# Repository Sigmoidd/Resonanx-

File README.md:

# Resonanx

**Resonanx** is the Cloudflare-ready build of the Resonance family music room for **Exodia Stage Hand**.

It is a performance-first, family-first app for music connection:

- family join-in rooms by code
- live player glow / target chord / session pulse
- gentle family reactions that feed into the sensory experience
- favorite performance saves
- solo, local duo, remote lead, remote player, and family join-in modes
- optional thermal band BLE support

## What changed in this patch

The previous family room prototype could fall back to local/shared storage. This patch adds a real Cloudflare relay path:

```txt
/api/room/:roomCode/presence
/api/room/:roomCode/live
/api/room/:roomCode/chord
/api/room/:roomCode/reaction
```

The Worker uses a Durable Object per room code. Family feedback is no longer just text:

- ✦ Spark creates a bloom pulse and soft chime.
- 👏 Applause creates a stronger bloom/audio/haptic/thermal pulse.
- ❤️ Love creates a warm halo, softer harmonic chime, haptic pattern, and optional thermal success pulse.

The language stays compassionate: family, player, performance, session, room, join-in. No medicalized family UI.

## Local dev

```bash
npm install
npm run dev
```

Local dev uses the app normally. If the `/api/room` relay is unavailable, room state falls back to local prototype storage so the UI can still be tested.

## Cloudflare deploy

```bash
npm install
npm run build
npx wrangler login
npx wrangler deploy
```

This deploys one Cloudflare Worker that serves both:

1. the React/Vite static app from `dist/`
2. the Durable Object family relay under `/api/room/...`

## Repo structure

```txt
src/App.jsx          Main Resonance / Resonanx app
src/main.jsx         Vite React entrypoint
worker/index.js      Cloudflare Worker + Durable Object relay
wrangler.toml        Cloudflare Worker config
docs/cloudflare.md   Deployment notes
```

## Cloudflare binding

`wrangler.toml` defines:

```toml
[[durable_objects.bindings]]
name = "RESONANCE_ROOMS"
class_name = "ResonanceRoom"
```

Each room code maps to its own Durable Object instance.

## GitHub quick start

```bash
git init
git add .
git commit -m "Launch Resonanx family relay build"
git branch -M main
git remote add origin https://github.com/Sigmoidd/resonanx.git
git push -u origin main
```

If the GitHub repo does not exist yet, create `Sigmoidd/resonanx` first, then run the push commands.

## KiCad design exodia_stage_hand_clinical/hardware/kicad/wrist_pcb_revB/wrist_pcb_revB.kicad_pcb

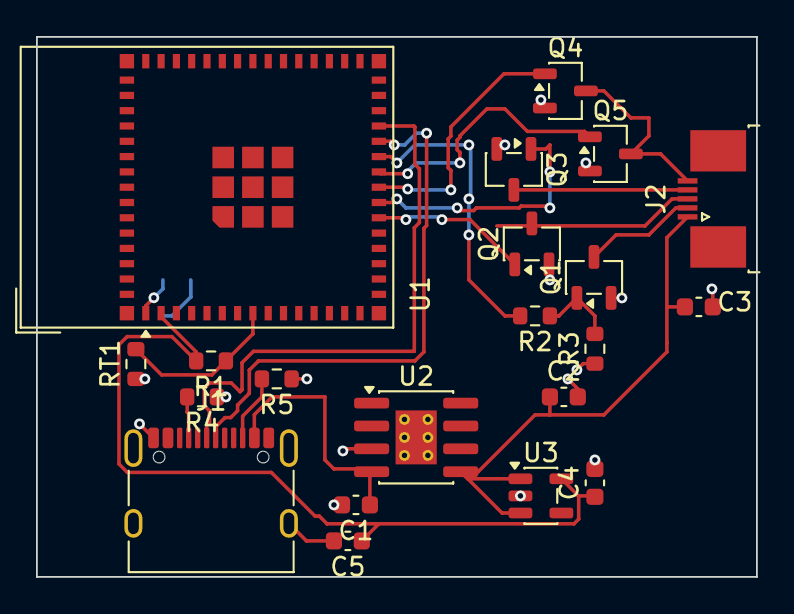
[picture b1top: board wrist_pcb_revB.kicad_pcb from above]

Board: 2 copper layers, 40.0 x 30.0 mm, 22 parts (1 on the bottom side), 19 nets.

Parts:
C1, C2, C5: 10uF; C_0603_1608Metric
C3, C4: 1uF; C_0603_1608Metric
C6: 0.1uF; C_0603_1608Metric
J1: USBC_16PIN; USB_C_Receptacle_XKB_U262-16XN-4BVC11
J2: ZIF_5PIN; TE_0-1734839-5_1x05-1MP_P0.5mm_Horizontal
Q1: AO3400A; SOT-23-3
Q2, Q3, Q4, Q5: 2N7002; SOT-23-3
R1: 10K; R_0603_1608Metric
R2: 100; R_0603_1608Metric
R3: 100K; R_0603_1608Metric
R4, R5: 5.1K; R_0603_1608Metric
RT1: NTC; R_0603_1608Metric
U1: ESP32S3_MODULE; ESP32-S2-MINI-1
U2: TP4056_IC; SOIC-8-1EP_3.9x4.9mm_P1.27mm_EP2.29x3mm_ThermalVias
U3: AP2112K; SOT-23-5

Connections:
/3V3: C4.1, C5.1, C6.1, R1.2, U1.2 (3V3), U3.5 (VOUT)
/ADC_NTC: R1.1, RT1.2, U1.8 (ADC_NTC)
/BAT+: C2.1, C3.1, J2.1 (V+), U2.5 (BAT+), U3.1 (VIN), U3.3 (EN)
/GATE_HEAT: Q1.1 (G), R2.1, R3.2
/GND: C1.2, C2.2, C3.2, C4.2, C5.2, C6.2, J1.A1 (GND), J1.A12 (GND), J1.B1 (GND), J1.B12 (GND), J1.SH (SHIELD), Q1.2 (S), Q2.2 (S), Q3.2 (S), Q4.2 (S), Q5.2 (S), R3.1, R4.1, R5.1, RT1.1, U1.1 (GND), U2.3 (BAT-), U3.2 (GND)
/NET_CC1: J1.A5 (CC1), R4.2
/NET_CC2: J1.B5 (CC2), R5.2
/NET_HEAT: J2.2 (HEAT_GND), Q1.3 (D)
/NET_M_IDX: J2.3 (M_IDX_GND), Q2.3 (D)
/NET_M_MID: J2.4 (M_MID_GND), Q3.3 (D)
/NET_M_RNG_PNK: J2.5 (M_RNG_PNK), Q4.3 (D), Q5.3 (D)
/PWM_HEATER: R2.2, U1.25 (PWM_HEATER)
/PWM_M_IDX: Q2.1 (G), U1.21 (PWM_M_IDX)
/PWM_M_MID: Q3.1 (G), U1.22 (PWM_M_MID)
/PWM_M_PNK: Q5.1 (G), U1.24 (PWM_M_PNK)
/PWM_M_RNG: Q4.1 (G), U1.23 (PWM_M_RNG)
/USB_D+: J1.A6 (D+), U1.27 (USB_D+)
/USB_D-: J1.A7 (D-), U1.26 (USB_D-)
/VBUS: C1.1, J1.A4 (VBUS), J1.A9 (VBUS), J1.B4 (VBUS), J1.B9 (VBUS), U2.4 (VIN)

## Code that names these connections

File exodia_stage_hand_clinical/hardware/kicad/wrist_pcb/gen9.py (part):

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      (property "Datasheet" "" (id 3) (at 0 0 0) (effects (hide yes)))
      (symbol "ESP32S3_MODULE_0_1"
        (rectangle (start -10.16 -10.16) (end 10.16 10.16) (stroke (width 0) (type default)) (fill (type background)))
        (pin output line (at -15.24 5.08 0) (length 5.08) (name "PWM_HEATER") (number "42"))
        (pin passive line (at -15.24 2.54 0) (length 5.08) (name "ADC_NTC") (number "8"))
        (pin output line (at -15.24 0 0) (length 5.08) (name "PWM_M_IDX") (number "38"))
        (pin output line (at -15.24 -2.54 0) (length 5.08) (name "PWM_M_MID") (number "39"))
        (pin output line (at -15.24 -5.08 0) (length 5.08) (name "PWM_M_RNG") (number "40"))
        (pin output line (at -15.24 -7.62 0) (length 5.08) (name "PWM_M_PNK") (number "41"))
        (pin passive line (at 15.24 5.08 180) (length 5.08) (name "ADC_EMG") (number "20"))
        (pin bidirectional line (at 15.24 -2.54 180) (length 5.08) (name "USB_D-") (number "26"))
        (pin bidirectional line (at 15.24 -5.08 180) (length 5.08) (name "USB_D+") (number "27"))
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add_label("3V3", 91.44+10.16, 76.2-2.54, 0)    # VOUT

# U1 ESP32
add_label("PWM_HEATER", 152.4-15.24, 76.2-5.08, 180)
add_label("ADC_NTC", 152.4-15.24, 76.2-2.54, 180)
add_label("PWM_M_IDX", 152.4-15.24, 76.2, 180)
add_label("PWM_M_MID", 152.4-15.24, 76.2+2.54, 180)
add_label("PWM_M_RNG", 152.4-15.24, 76.2+5.08, 180)
add_label("PWM_M_PNK", 152.4-15.24, 76.2+7.62, 180)
add_label("ADC_EMG", 152.4+15.24, 76.2-5.08, 0)
add_label("USB_D-", 152.4+15.24, 76.2+2.54, 0)
add_label("USB_D+", 152.4+15.24, 76.2+5.08, 0)
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add_label("GND", 152.4+15.24, 76.2, 0)

# Gate Resistor R2 & Q1
add_label("PWM_HEATER", 152.4, 137.16-7.62, 90)
add_label("GATE_HEAT", 152.4, 137.16+7.62, 270)
add_label("GATE_HEAT", 172.72-7.62, 137.16, 180)
add_label("GND", 172.72+7.62, 137.16+2.54, 0)
add_label("NET_HEAT", 172.72+7.62, 137.16-2.54, 0)

# Pulldown R3
add_label("GATE_HEAT", 162.56, 147.32-7.62, 90)
add_label("GND", 162.56, 147.32+7.62, 270)

# Motors
add_label("PWM_M_IDX", 132.08-7.62, 167.64, 180)
add_label("GND", 132.08+7.62, 167.64+2.54, 0)
add_label("NET_M_IDX", 132.08+7.62, 167.64-2.54, 0)

add_label("PWM_M_MID", 152.4-7.62, 167.64, 180)
add_label("GND", 152.4+7.62, 167.64+2.54, 0)
add_label("NET_M_MID", 152.4+7.62, 167.64-2.54, 0)

add_label("PWM_M_RNG", 172.72-7.62, 167.64, 180)
add_label("GND", 172.72+7.62, 167.64+2.54, 0)
add_label("NET_M_RNG_PNK", 172.72+7.62, 167.64-2.54, 0)

add_label("PWM_M_PNK", 193.04-7.62, 167.64, 180)
add_label("GND", 193.04+7.62, 167.64+2.54, 0)
add_label("NET_M_RNG_PNK", 193.04+7.62, 167.64-2.54, 0)

# NTC Divider
add_label("3V3", 101.6, 137.16-7.62, 90)
add_label("ADC_NTC", 101.6, 137.16+7.62, 270)
add_label("ADC_NTC", 101.6, 157.48-7.62, 90)
add_label("GND", 101.6, 157.48+7.62, 270)

# ZIF J2
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
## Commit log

2026-05-13 Initialize Resonanx Cloudflare app
2026-05-13 Add project gitignore
2026-05-13 Add React entrypoint
2026-05-13 Add Vite HTML shell
2026-05-13 Add Resonanx family sensory app
2026-05-13 Add Cloudflare Worker config
2026-05-13 Add Durable Object room relay
2026-05-13 Add README
2026-05-13 Add Cloudflare deployment notes
2026-05-13 Add full V3 app source chunk 01
2026-05-15 Organize Exodia Stage Hand MVP assets into dedicated subdirectory
2026-05-15 Add Clinical Edition: flex PCB design for memory care deployment
2026-05-16 Fix KiCad schematic formatting to resolve parsing errors
2026-05-16 Replace schematic with minimal working template and add component checklist
2026-05-16 Generate valid KiCad schematic with UUIDs
2026-05-16 Auto-wire components using KiCad local labels and add ZIF/USB connectors
2026-05-16 Fix KiCad ERC errors (power flags, grid alignment, pin direction)
2026-05-16 Fix final KiCad ERC issues with power conflicts and label positioning
2026-05-16 Fix footprint mapping errors by using exact physical pad numbering
2026-05-16 Auto-place PCB components and add board outline
2026-05-16 Update physical ESP32 pin mappings (28/29/30/64/45) and exact USB pad mapping
2026-05-16 Schematic v1.6: 16-pin USB, LDO, Gate Resistors, CC Resistors
2026-05-17 PCB v1.6: Wiped traces, auto-placed new components
2026-05-18 Schematic v1.7: AO3400A Heater MOSFET, Netclasses (power_high, signal_data)
2026-05-18 Schematic v1.8: Decoupling Capacitors (TP4056, LDO, ESP32)
2026-05-18 Schematic v1.9: Re-mapped motor and heater gates to right-facing GPIOs (21-25) for optimized PCB routing
2026-05-18 Schematic v1.9: Re-applied GPIO 21-25 mappings cleanly on disk
2026-05-18 Schematic v1.9: Fixed Python code replacement bug and correctly re-mapped pins to 21-25
2026-05-18 Schematic v1.10: Reverted Q4 (PWM_M_RNG) back to Pin 40 to preserve active trace, other pins kept on safe 21-25
2026-05-19 Add Exodia Wrist PCB Rev B and update schematic/layout; clean up .history submodule and optimize .gitignore for KiCad
2026-05-20 Implement Exodia Stage Hand Care Rev B: 20-pin ZIF, triple haptic trigger architecture, ground isolation, and care vocabulary
2026-05-20 Configure power_high and signal_data netclass rules in wrist_pcb_revB project settings
2026-05-20 Resolve footprint loading errors by aligning MSOP-10 and TE FPC footprint prefixes with KiCad 10 standard libraries
2026-05-20 Correct schematic file reference to wrist_pcb_revB.kicad_sch in project settings to enable accurate netlist syncing
